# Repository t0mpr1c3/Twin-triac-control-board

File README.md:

Twin-triac-control-board
========================

Control board for two triacs in TO-220 package on Dangerous Prototypes DP5050 standard size PCB

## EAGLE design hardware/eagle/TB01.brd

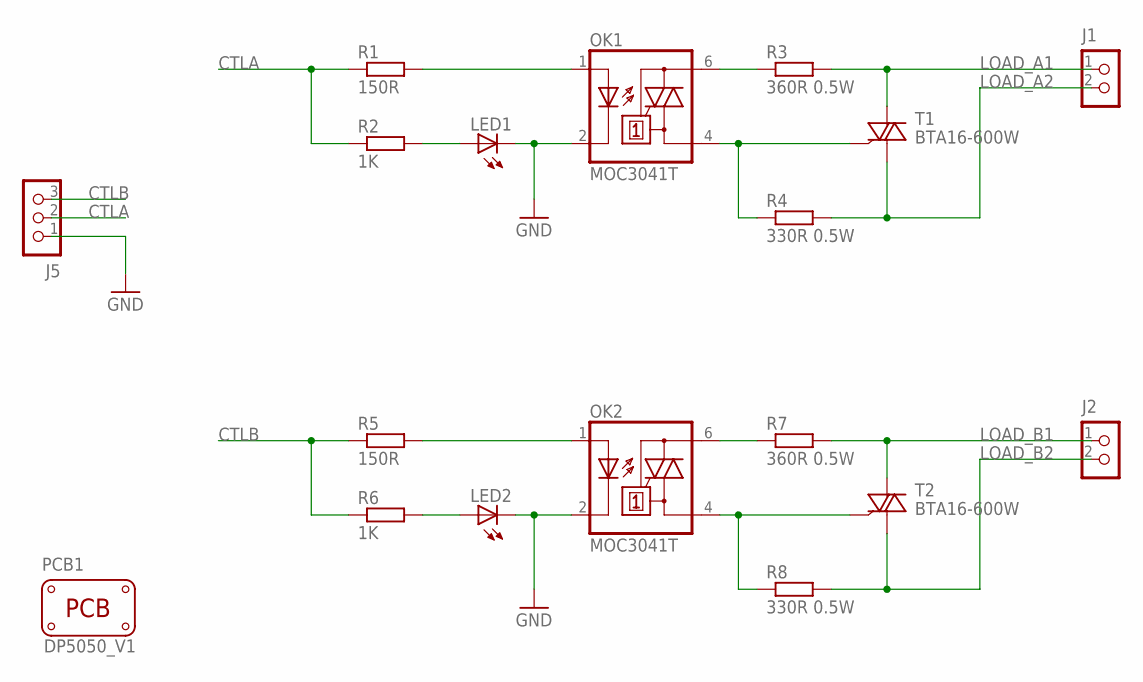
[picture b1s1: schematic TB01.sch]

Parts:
J1, J2: CON_TERMINAL_BLOCK_02-5MM; TERMINAL_BLOCK_2P_5
J5: CON_TERMINAL_BLOCK_03-5MM; TERMINAL_BLOCK_3P_5
LED1, LED2: LED3MM
OK1, OK2: MOC3041T; DIL06B
PCB1: PCB_DP_SQUARE-5X5; DP5050_V1
R1, R5: 150R; 0207/7
R2, R6: 1K; 0207/7
R3, R7: 360R 0.5W; 0411V
R4, R8: 330R 0.5W; 0411V
T1, T2: BTA16-600W; TO220DSH

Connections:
CTLA: J5.2, R1.1, R2.1
CTLB: J5.3, R5.1, R6.1
GND: J5.1, LED1.K (C), LED2.K (C), OK1.2 (C), OK2.2 (C)
LOAD_A1: J1.1, R3.2, T1.A2
LOAD_A2: J1.2, R4.2, T1.A1
LOAD_B1: J2.1, R7.2, T2.A2
LOAD_B2: J2.2, R8.2, T2.A1
unnamed: LED1.A, R2.2
unnamed: OK1.1 (A), R1.2
unnamed: OK1.6 (A2), R3.1
unnamed: OK2.6 (A2), R7.1
unnamed: OK1.4 (A1), R4.1, T1.G
unnamed: LED2.A, R6.2
unnamed: OK2.4 (A1), R8.1, T2.G
unnamed: OK2.1 (A), R5.2

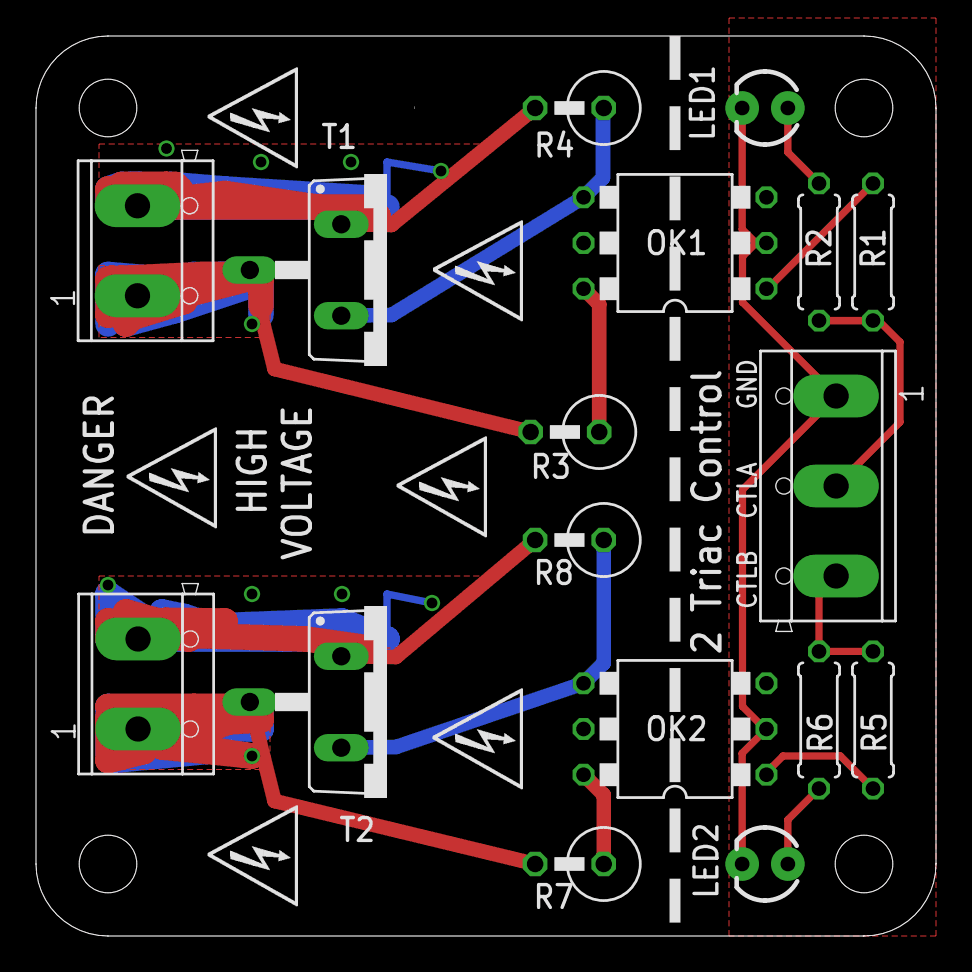
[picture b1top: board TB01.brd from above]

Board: 4 copper layers, 50.0 x 50.0 mm, 19 parts (1 on the bottom side), 15 nets.

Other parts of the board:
U$2: OSHW-LOGO-M

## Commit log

2013-11-24 TB01 first draft
2013-11-24 layout altered, resistor values
2013-11-25 high voltage warning
2013-11-26 redesign without snubbers
2013-11-27 splay pin triac package

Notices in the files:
hardware/eagle/TB01.brd:
CC BY-SA 3.0
